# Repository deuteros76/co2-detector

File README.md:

# CO2 detector

After reading [this article](https://theconversation.com/how-to-use-ventilation-and-air-filtration-to-prevent-the-spread-of-coronavirus-indoors-143732) ([ES](https://www.bbc.com/mundo/noticias-53754274)) I started to think about creating my own sensor board. I searched which sensor to use and the SGP30 seemed a good option to me. After a few tests, I modified the code of another project and then I built two prototypes which are currently working in my house. The device uses a mqtt queue to send data to an IoT gateway (a minipc running Home Assistant in my case). In addition to that, there are three LEDs to show what is the current state of the air based on CO2 PPMs:

- Green light is shown if there are less than 600 PPM of CO2.
- Yellow light if there are between 600 and 800 PPM.
- Red when the CO2 is greater than 800.

## Features
- Configuration of WiFi network and MQTT through a web portal.
- Temperature, humidity and air qualiity (CO2 and TVOC) sensors.
- Possibility of being used with Home Assistant or any software capable of reading a mqtt queue.

## License

### Hardware

You will find the hardware schematics and design files in the board directory. The hardware is distributed under the Cern Open Source Hardware License 1.2.

### Software

The software is available unde Apache 2.0 license and can be found in the co2-detector directory.

### Documentation

Documents found in this project are distrubuted under Creative Commons CC0 license.

## Hardware components
- Wemos D1 mini
- DHT22 sensor
- SGP30 sensor
- Wires, tools...
- Green, yellow and red LEDs
- ... (See bill of materials below)

## Software requirements
- This source uses Arduino IDE and its standard libraries
- Additional libraries: WiFiManager, Arduino Json, PubSubClient, DHT and Adafruit SGP30
- A computer running MQTT
- [Optional] A computer running Home Assistant

## Device configuration

During the first execution, the device will launch a WiFi access point. Using your PC or mobile device, check the available networks and connect to the network whose name starts with "CO2-detector". After that, point your browser to http://192.168.4.1 and the configuration page will be displayed. 

Choose the first option ("Configure WiFi") and select your WiFi network from the list of detected access points then, write your WiFi password. If your wifi network is open, leave the password field empty.

Now configure you network settings.

The device will publish all sensor data through mqtt so, the information is sent to another machine such as a minipc used as an IoT gatway. To do that, you have to introduce the data of the mqtt server. 

Then, fill all the fields related to your MQTT topic names and save your configuration. If you have several devices in different places you can change the prefix (room1/Temperature, room2/Temperature and so on).

After saving the settings the device will be reset and then it will run in its normal mode, gathering data from all sensors.

## Usage

All LEDs will be turned on when the device starts. After configuring the device, it will try to connect to the configured network. After that, only one LED will be lighted.
  
The CO2 sensor takes a measurement every second and sends an average of the last 60 CO2 and TVOC values every minute. The temperature and humidity sensor is used to correct the obtained data as explained in the SGP30 data sheet.

Device's LEDs are also useful to know the current state in case of error: 

  1.  If you see all them lighted on, the board is unable to connect to your WiFi.
  2.  If the yellow LED blinks, your co2-detector is connected to the WiFi but cannot reach the MQTT queue.
  3.  If the SGP30 sensor is not detected, the red LED blinks.

DHT22 (humidity and temperature sensor) errors are detected but not reported through the LEDs as this sensor is used to improve the accuracy of the CO2 readings but it is not critical if it doesn't work. It is possible to detect a malfunction in the DHT22 finding the last temperature and humidity readings in Homa Assistant (for instance if both values are not updated for many hours). 

## Home Assistant

I use Home Assistant to collect all the data and display the information. The software runs in a miniPC (a SolidRun CuBox-i) which is a small home IoT server and also has the Mosquitto mqtt broker. The device sends sensors data to the mqtt broker and Home Assistant reads it and stores everything in a data base. 
In addition to that Home Assistant has a frontend application that shows the current status of all your sensors and historical graphs of a selected day.
You can use any other similar software with the capability of subscribing to read from mqtt.

# Bill of materials

| Reference |  Value                     |  Footprint                                                     |  Datasheet |
| --------- | -------------------------- | -------------------------------------------------------------- | ---------- |
| D1        | Red                        | LEDs:LED_D5.0mm                                                |            |
| R3        | 90                         | Resistors_THT:R_Axial_DIN0207_L6.3mm_D2.5mm_P7.62mm_Horizontal |            |
| R4        | 10K                        | Resistors_THT:R_Axial_DIN0207_L6.3mm_D2.5mm_P7.62mm_Horizontal |            |
| TH1       | DHT22_Temperature_Humidity | Sensors:DHT22_Temperature_Humidity                             |            |
| U2        | SGP30                      | Pin_Headers:Pin_Header_Straight_1x04_Pitch2.54mm               |            |
| D2        | Yellow                     | LEDs:LED_D5.0mm                                                |            |
| D3        | Green                      | LEDs:LED_D5.0mm                                                |            |
| R1        | 160                        | Resistors_THT:R_Axial_DIN0207_L6.3mm_D2.5mm_P7.62mm_Horizontal |            |
| R2        | 160                        | Resistors_THT:R_Axial_DIN0207_L6.3mm_D2.5mm_P7.62mm_Horizontal |            |
| U1        | WeMos_D1_mini              | wemos-d1-mini:wemos-d1-mini-with-pin-header                    |            |

# Example of a configuration for Home Assistant
The following Home Assistant configuration file is an example of two CO2 detectors placed at different rooms within a house. One is in a dinner room while the second is monitoring a sleeping room. Each device sends the data provided by the SGP20 (CO2 and TVOC) and DHT22 (temperature, humidity and heat index) sensors to a mqtt queue which is installed in the computer hosting Home Assistant.

```
homeassistant:
  # Name of the location where Home Assistant is running
  name: Home
  # Impacts weather/sunrise data
  elevation: 50
  # C for Celsius, F for Fahrenheit
  temperature_unit: C
  # 'metric' for the metric system, 'imperial' for the imperial system
  unit_system: metric
  # Pick yours from here: http://en.wikipedia.org/wiki/List_of_tz_database_time_zones
  time_zone: Europe/Madrid

# Show links to resources in log and frontend
#introduction:

system_health:

group:
  kids:
    name: Kids room
    entities:
      - sensor.kids_temperature
      - sensor.kids_humidity
      - sensor.kids_heatindex
      - sensor.kids_co2
      - sensor.kids_tvoc
  dinner_room:
    name: Dinner room
    entities:
      - sensor.comedor_temperature
      - sensor.comedor_humidity
      - sensor.comedor_heatindex
      - sensor.comedor_co2
      - sensor.comedor_tvoc

# Enables the frontend
frontend:

# Checks for available updates
updater:

# Discover some devices automatically
discovery:

# Allows you to issue voice commands from the frontend in enabled browsers
conversation:

# Enables support for tracking state changes over time.
history:

# View all events in a logbook
logbook:

#MQTT configuration
mqtt:
  broker: 127.0.0.1
  port: 1883
  client_id: home-assistant-1
  keepalive: 60
  #username: USERNAME
  #password: PASSWORD
  #certificate: /home/username/dev/addtrustexternalcaroot.crt
  protocol: 3.1

##### Kids room  #####
sensor kids_temperature:
   platform: mqtt
   name: "Kids temperature"
   state_topic: "kids/temperature"
   qos: 0
   unit_of_measurement: "C"

sensor kids_humidity:
   platform: mqtt
   name: "Kids humidity"
   state_topic: "kids/humidity"
   qos: 0
   unit_of_measurement: "%"

sensor kids_heatindex:
   platform: mqtt
   name: "Kids heatindex"
   state_topic: "kids/heatindex"
   qos: 0
   unit_of_measurement: "C"

sensor kids_co2:
   platform: mqtt
   name: "Kids CO2"
   state_topic: "kids/co2"
   qos: 0
   unit_of_measurement: "ppm"
                      
sensor kids_tvoc:
    platform: mqtt
    name: "Kids TVOC"
    state_topic: "kids/tvoc"
    qos: 0
    unit_of_measurement: "ppb"

##### Dinner room #####
sensor comedor_temperature:
    platform: mqtt
    name: "Dinner room temperature"
    state_topic: "comedor/temperature"
    qos: 0
    unit_of_measurement: "C"

sensor comedor_humidity:
    platform: mqtt
    name: "Dinner room humidity"
    state_topic: "comedor/humidity"
    qos: 0
    unit_of_measurement: "%"

sensor comedor_heatindex:
    platform: mqtt
    name: "Dinner room heatindex"
    state_topic: "comedor/heatindex"
    qos: 0
    unit_of_measurement: "C"

sensor comedor_co2:
    platform: mqtt
    name: "Dinner room CO2"
    state_topic: "comedor/co2"
    qos: 0
    unit_of_measurement: "ppm"
                         
sensor comedor_tvoc:
    platform: mqtt
    name: "Dinner room TVOC"
    state_topic: "comedor/tvoc"
    qos: 0
    unit_of_measurement: "ppb"

#config:

#mobile_app:

recorder:
    db_url: postgresql://user:password@localhost/hass
```

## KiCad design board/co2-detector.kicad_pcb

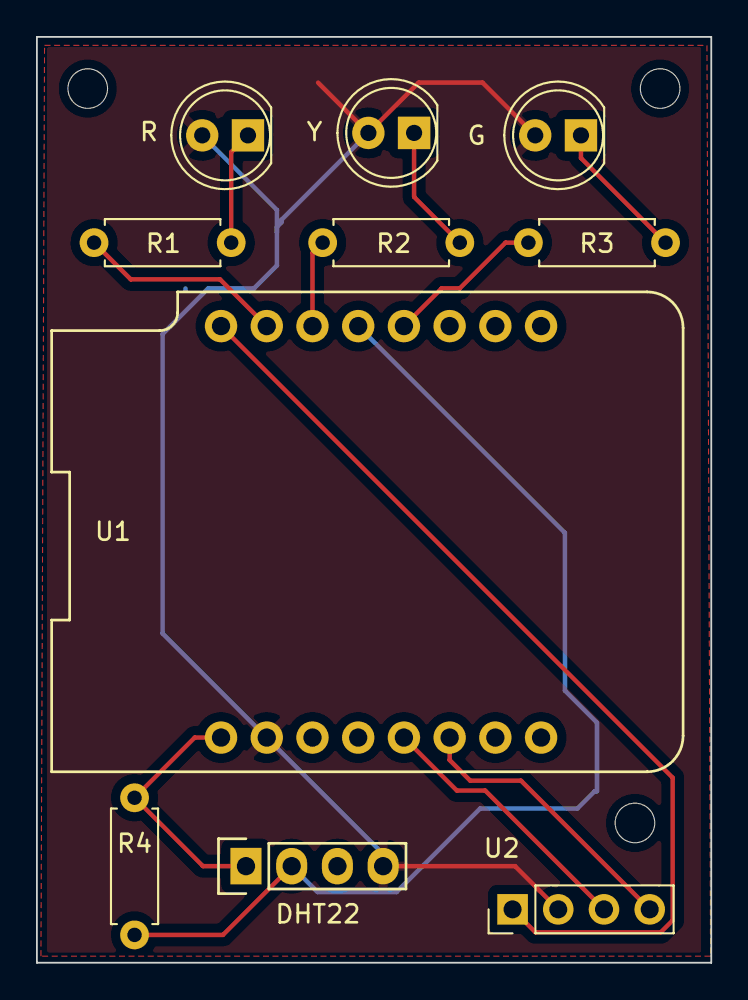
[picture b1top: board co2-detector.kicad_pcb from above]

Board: 2 copper layers, 37.5 x 51.4 mm, 10 parts (0 on the bottom side), 12 nets.

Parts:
DHT22: DHT22_Temperature_Humidity
G: Green; LED_D5.0mm
R: Red; LED_D5.0mm
R1, R2: 160; R_Axial_DIN0207_L6.3mm_D2.5mm_P7.62mm_Horizontal
R3: 90; R_Axial_DIN0207_L6.3mm_D2.5mm_P7.62mm_Horizontal
R4: 10K; R_Axial_DIN0207_L6.3mm_D2.5mm_P7.62mm_Horizontal
U1: WeMos_D1_mini; wemos-d1-mini-with-pin-header
U2: SGP30; Pin_Header_Straight_1x04_Pitch2.54mm
Y: Yellow; LED_D5.0mm

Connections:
/3.3V: U1.8, U2.1
/5V: DHT22.1, R4.1, U1.9
/GND: DHT22.4, G.2, R.2, U1.10, U2.2, Y.2
unnamed: R.1, R1.1
unnamed: R2.1, Y.1
unnamed: G.1, R3.1
unnamed: R1.2, U1.7
unnamed: R2.2, U1.6
unnamed: R3.2, U1.4
unnamed: DHT22.2, R4.2, U1.5
unnamed: U1.13, U2.3
unnamed: U1.14, U2.4

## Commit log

2020-10-21 Licenses for hw and sw
2020-10-21 Starting the readme
2020-10-21 Readme corrections
2020-10-23 Documenting...
2020-10-23 AP name changed
2020-10-23 Documentation updated
2020-10-23 Typos fixed
2020-10-23 Another typo
2020-11-11 Board revision 2, fixes two desing problems
2020-12-09 LED pins changed. All LEDs will be on when the device is started
2020-12-09 Home assistant sample configuration file
2020-12-09 More information in the Readme.md
2020-12-09 Fixing typos
2020-12-10 Structure changed
2021-01-22 Comment corrected
2021-01-22 More information through LEDs. Yellow blinks if the device is unable to connect to the mqtt queue
2021-01-22 Yellow blinking LED documented
2021-01-22 Blink red LED y co2 sensor is not detected
2021-01-22 Better control of the yellow LED in case of MQTT error
2021-01-22 Switch on the green LED after configuration
2021-01-22 Detect DHT22 errors and avoid humidity compensation in case on NAN values
2021-01-22 Do not send NaN values from the DHT22 to the queue
2021-01-22 Documentation updated. More information about errors detection
2021-01-23 Add a host name. I'm not sure if it works
2021-01-24 Now it is possible to connect to an open network. Better management of the connection process.
2021-01-24 How to connect to an open network
2021-01-24 Print device mac address
2022-08-13 fix: use conuter variable to obtain the number of iterations needed before showing sensor information
2022-09-01 feat: use discovery messages to announce the device in Home Assistant
2022-09-02 feat: print hostname on serial port
2022-09-07 fix: different discovery problems solved
2022-09-20 fix: hostname prefix fixed
2022-12-07 fix: force to disconnect when the connection is lost
2022-12-08 fix: removed useless disconnect calls
2022-12-08 fix: the timeout chech didn't make sense. It was created for saving energy using a deepsleep mode that is not implemented
